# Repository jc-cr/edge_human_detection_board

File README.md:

# edge_human_detection_board
Board used

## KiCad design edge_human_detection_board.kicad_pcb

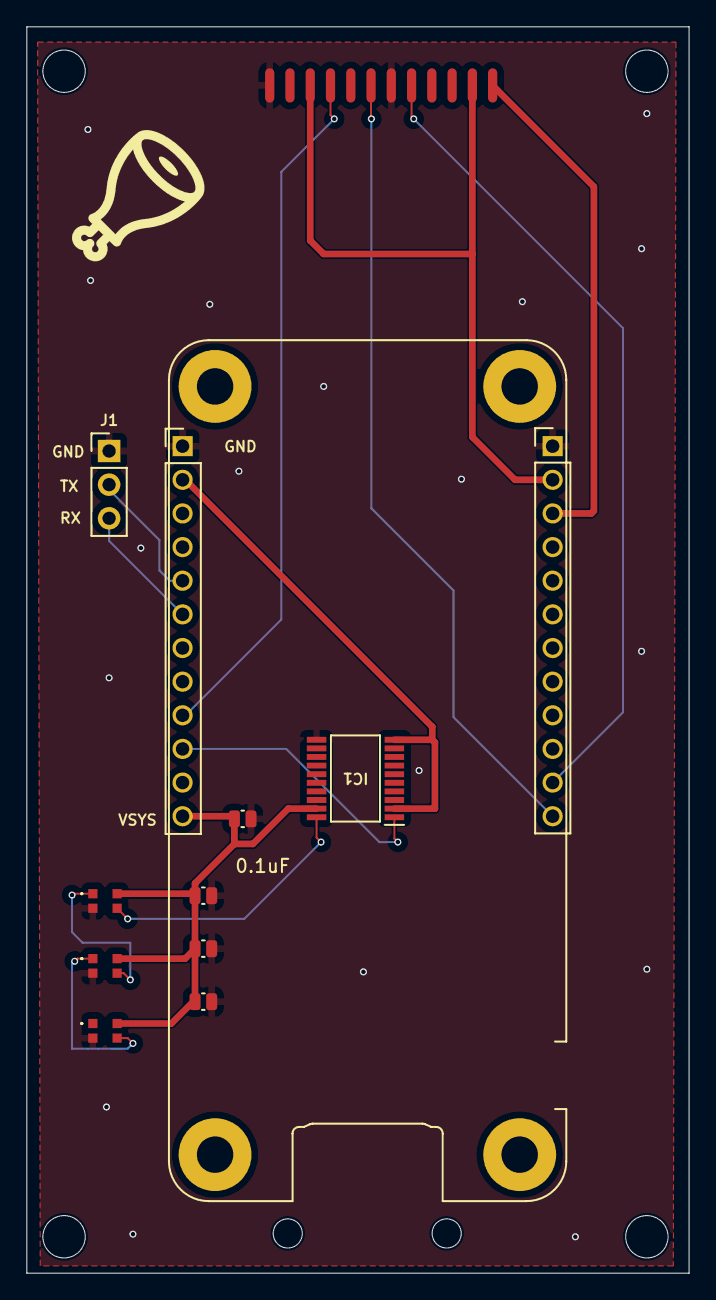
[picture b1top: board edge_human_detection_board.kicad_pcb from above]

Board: 4 copper layers, 50.0 x 94.1 mm, 11 parts (0 on the bottom side), 14 nets.

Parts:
C1, C2, C3, C4: 0.1uF; C_0504_1310Metric_Pad0.83x1.28mm_HandSolder
D2, D3, D4: WS2812B; 4684
IC1: TXB0108PWR; SOP65P640X120-20N
J1: Conn_01x03_Socket; PinHeader_1x03_P2.54mm_Vertical
U1: coral_micro_board_mating
U2: SATEL-VL53L8A

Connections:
/Coral Micro Breakouts/+1.8VDC_RGB: IC1.2 (VCCA), IC1.10 (OE), U1.14 (1.8V)
/Coral Micro Breakouts/+1.8VDC_TOF: U1.2 (1.8V), U2.3 (CORE_1V8), U2.11 (IOVDD)
/Coral Micro Breakouts/+3.3VDC: U1.3 (3.3V), U2.12 (AVDD)
/Coral Micro Breakouts/+5VDC: C1.2, C2.2, C3.2, C4.2, D2.4 (VDD), D3.4 (VDD), D4.4 (VDD), IC1.19 (VCCB), U1.24 (VSYS)
/Coral Micro Breakouts/DEBUG_RX: J1.3, U1.18 (UART6_RX)
/Coral Micro Breakouts/DEBUG_TX: J1.2, U1.17 (UART6_TX)
/Coral Micro Breakouts/PWM_1: U1.21 (PWM_B), U2.4 (LPn)
/Coral Micro Breakouts/SCL: U1.11 (I2C1_SCL), U2.8 (SCL)
/Coral Micro Breakouts/SDA: U1.12 (I2C1_SDA), U2.6 (SDA)
/RGB Signalling/SIG_IN_PWM0: IC1.1 (A1), U1.22 (PWM_A)
/RGB Signalling/SIG_IN_RGB1: D2.3 (DI), IC1.20 (B1)
/RGB Signalling/SIG_IN_RGB2: D2.1 (DO), D3.3 (DI)
/RGB Signalling/SIG_IN_RGB3: D3.1 (DO), D4.3 (DI)
GND: C1.1, C2.1, C3.1, C4.1, D2.2 (GND), D3.2 (GND), D4.2 (GND), IC1.11 (GND), J1.1, U1.1 (GND), U1.13 (GND), U2.1 (DUT_GND), U2.7 (I2C_N)

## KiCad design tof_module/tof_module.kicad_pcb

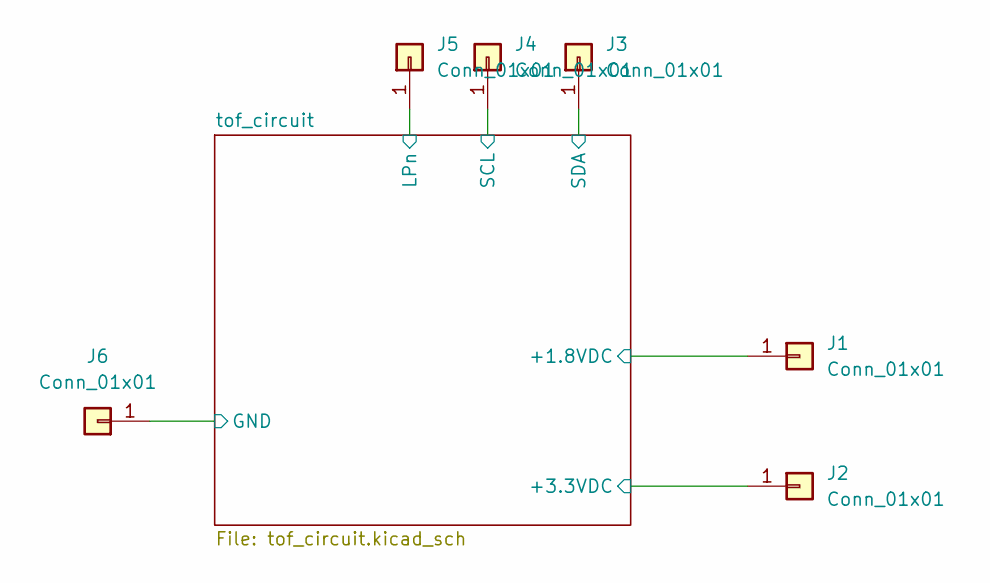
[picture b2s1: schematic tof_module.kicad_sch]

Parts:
J1, J2, J3, J4, J5, J6: Conn_01x01; spec_header

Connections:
/tof_circuit/AVDD: J2.1; also elsewhere on the board
/tof_circuit/CORE_1V8: J1.1; also elsewhere on the board
/tof_circuit/LPn: J5.1; also elsewhere on the board
/tof_circuit/SCL: J4.1; also elsewhere on the board
/tof_circuit/SDA: J3.1; also elsewhere on the board
GND: J6.1; also elsewhere on the board

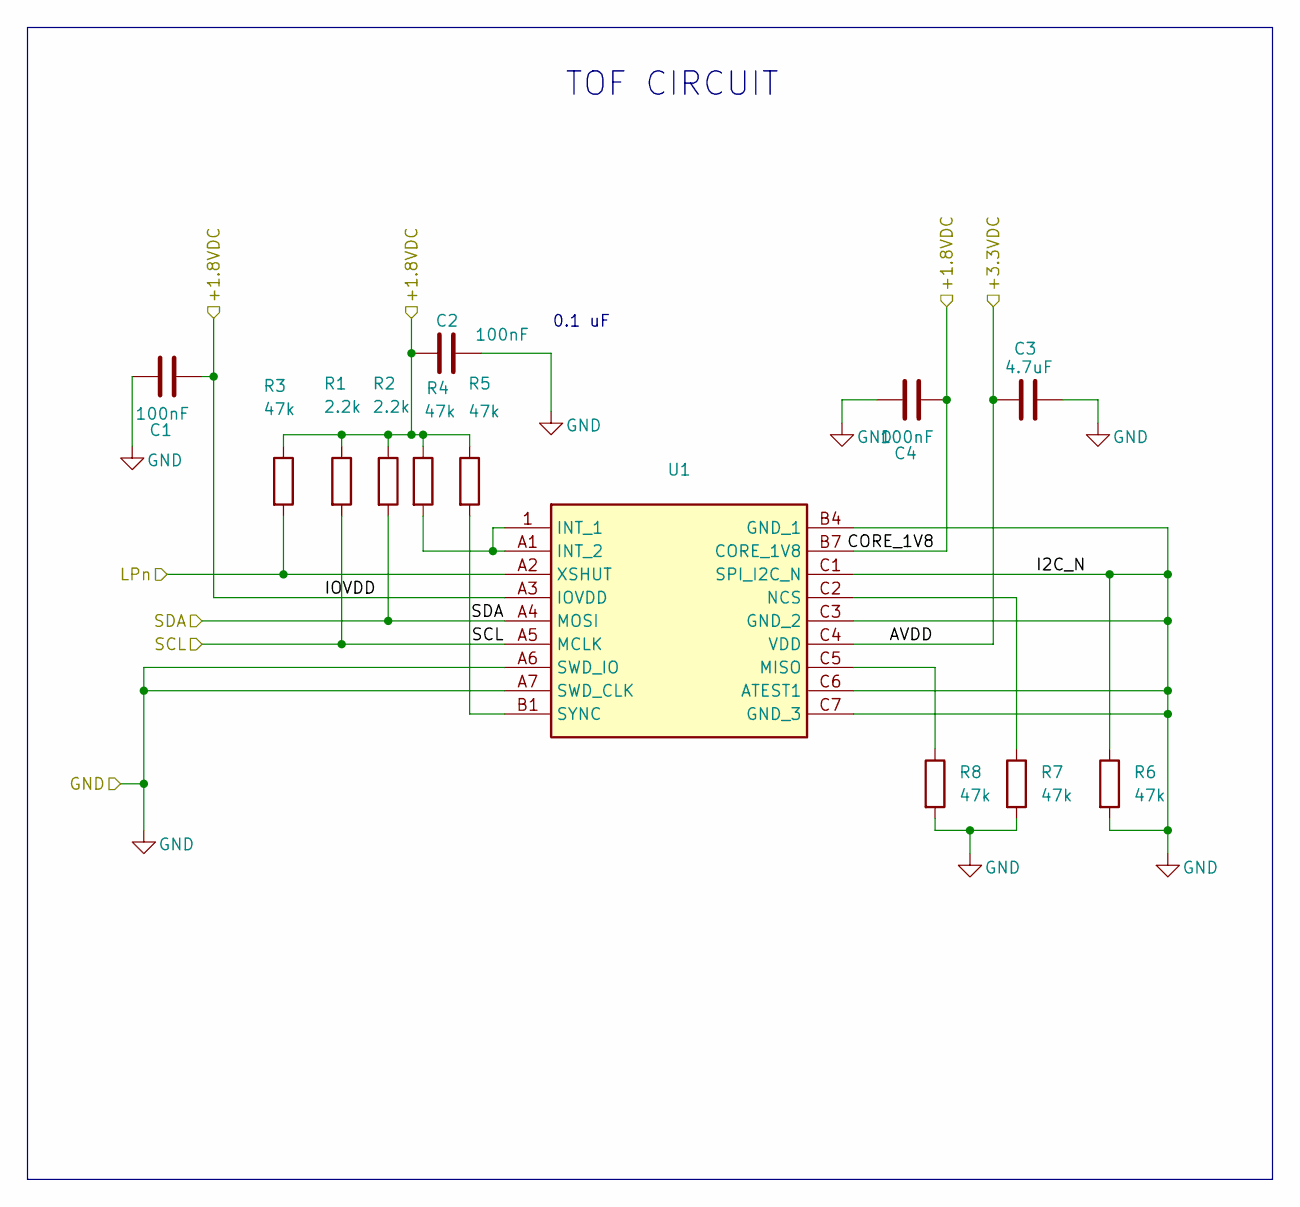
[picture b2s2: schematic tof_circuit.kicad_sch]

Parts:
C1, C2, C4: 100nF; C_0201_0603Metric_Pad0.64x0.40mm_HandSolder
C3: 4.7uF; C_0201_0603Metric_Pad0.64x0.40mm_HandSolder
R1, R2: 2.2k; R_0603_1608Metric_Pad0.98x0.95mm_HandSolder
R3, R4, R5, R6, R7, R8: 47k; R_0603_1608Metric_Pad0.98x0.95mm_HandSolder
U1: VL53L8CXV0GC1; Mouser Part Number 511-VL53L8CXV0GC/1

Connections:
/tof_circuit/AVDD: C3.1, U1.C4 (VDD); also elsewhere on the board
/tof_circuit/CORE_1V8: C1.1, C2.2, C4.1, R1.1, R2.1, R3.1, R4.1, R5.1, U1.A3 (IOVDD), U1.B7 (CORE_1V8); also elsewhere on the board
/tof_circuit/LPn: R3.2, U1.A2 (XSHUT); also elsewhere on the board
/tof_circuit/SCL: R1.2, U1.A5 (MCLK); also elsewhere on the board
/tof_circuit/SDA: R2.2, U1.A4 (MOSI); also elsewhere on the board
GND: C1.2, C2.1, C3.2, C4.2, R6.1, R6.2, R7.2, R8.2, U1.A6 (SWD_IO), U1.A7 (SWD_CLK), U1.B4 (GND_1), U1.C1 (SPI_I2C_N), U1.C3 (GND_2), U1.C6 (ATEST1), U1.C7 (GND_3); also elsewhere on the board
unnamed: R4.2, U1.1 (INT_1), U1.A1 (INT_2)
unnamed: R8.1, U1.C5 (MISO)
unnamed: R7.1, U1.C2 (NCS)
unnamed: R5.2, U1.B1 (SYNC)

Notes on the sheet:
TOF CIRCUIT
0.1 uF

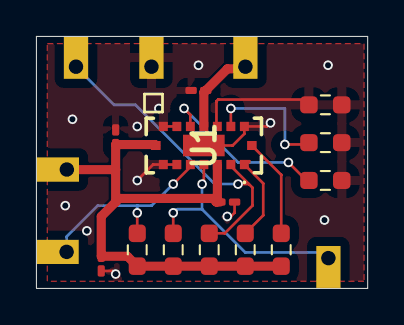
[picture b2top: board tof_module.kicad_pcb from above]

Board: 2 copper layers, 18.4 x 14.0 mm, 19 parts (0 on the bottom side), 10 nets.

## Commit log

2024-11-22 Init
2024-11-24 working on board
2024-11-24 made board
2024-12-29 working on revisions
2025-01-11 latest
2025-01-13 Fab v
2025-02-22 not working, reverting to old design
2025-02-22 latest updates, up to v2
